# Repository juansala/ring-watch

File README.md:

# ring-watch

A watch that fits on your finger. Features an ATtiny85 and the PCF8523 real-time clock IC to change the color of an RGB LED based on the time of day.

Libraries:

TinyBMP280
SoftwareSerial
TinyWireM
RTCLib

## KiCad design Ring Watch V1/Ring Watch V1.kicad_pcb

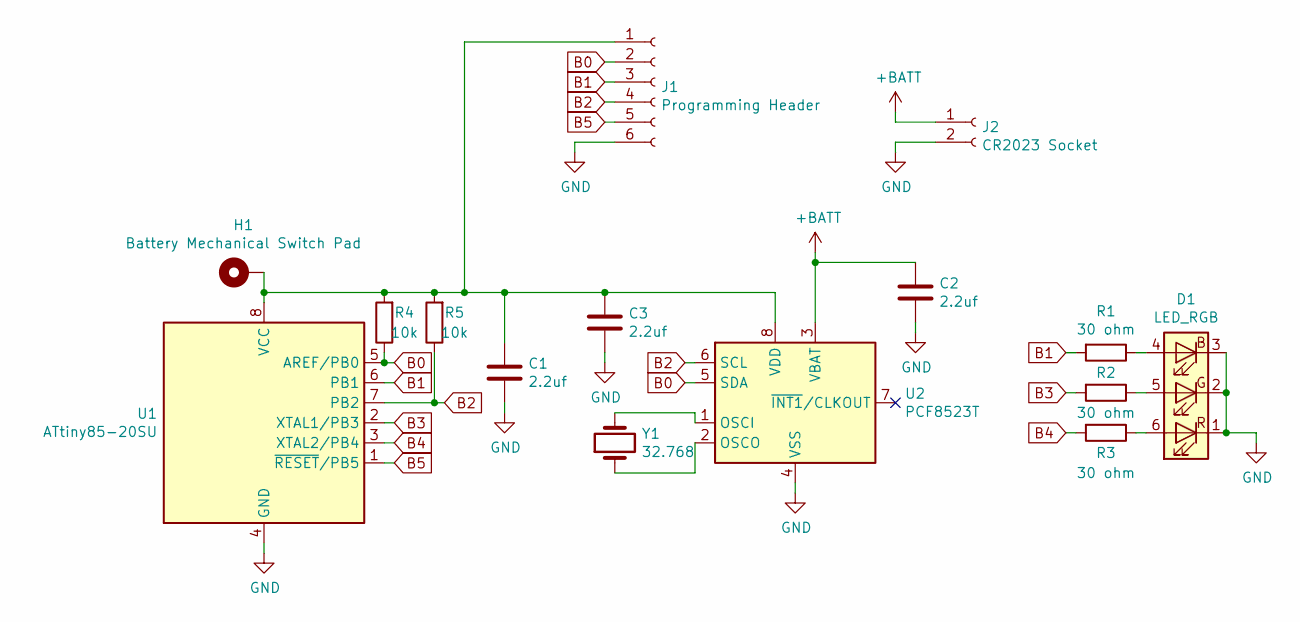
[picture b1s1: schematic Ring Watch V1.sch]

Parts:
C1, C2, C3: 2.2uf; C_0805_2012Metric_Pad1.15x1.40mm_HandSolder
D1: LED_RGB; LED_RGB_5050-6
H1: Battery Mechanical Switch Pad; TestPoint_Keystone_5019_Minature
J1: Programming Header; PinHeader_2x03_P1.00mm_Vertical
J2: CR2023 Socket; BatteryHolder_Keystone_3034_1x20mm
R1, R2, R3: 30 ohm; R_0805_2012Metric_Pad1.15x1.40mm_HandSolder
R4, R5: 10k; R_0805_2012Metric_Pad1.15x1.40mm_HandSolder
U1: ATtiny85-20SU; SOIJ-8_5.3x5.3mm_P1.27mm
U2: PCF8523T; SOIC-8_3.9x4.9mm_P1.27mm
Y1: 32.768; Crystal_SMD_3215-2Pin_3.2x1.5mm

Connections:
+BATT: C2.1, J2.1, U2.3 (VBAT)
B0: J1.2, R4.1, U1.5 (AREF/PB0), U2.5 (SDA)
B1: J1.3, R1.2, U1.6 (PB1)
B2: J1.4, R5.1, U1.7 (PB2), U2.6 (SCL)
B3: R2.2, U1.2 (XTAL1/PB3)
B4: R3.2, U1.3 (XTAL2/PB4)
B5: J1.5, U1.1 (~RESET~/PB5)
GND: C1.2, C2.2, C3.2, D1.1 (RK), D1.2 (GK), D1.3 (BK), J1.6, J2.2, U1.4 (GND), U2.4 (VSS)
unnamed: C1.1, C3.1, H1.1, J1.1, R4.2, R5.2, U1.8 (VCC), U2.8 (VDD)
unnamed: D1.4 (BA), R1.1
unnamed: D1.5 (GA), R2.1
unnamed: D1.6 (RA), R3.1
unnamed: U2.1 (OSCI), Y1.2
unnamed: U2.2 (OSCO), Y1.1

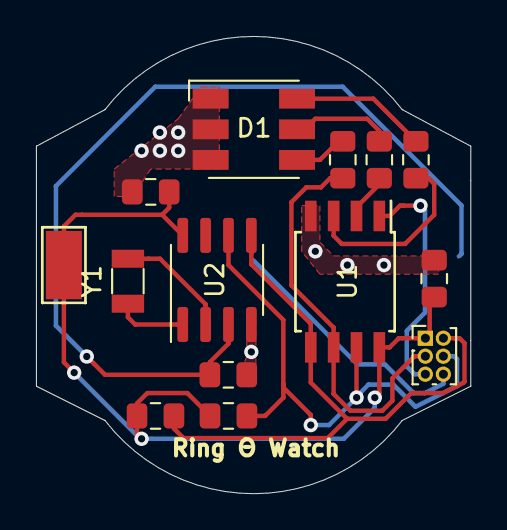
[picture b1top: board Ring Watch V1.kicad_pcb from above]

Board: 2 copper layers, 24.1 x 25.4 mm, 15 parts (1 on the bottom side), 14 nets.

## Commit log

2020-11-22 added KiCad project folder
2020-11-22 changed to ATtiny85, maybe use RGB first
2020-11-23 new mechanical switch design for input power to micro
2020-11-23 almost done placing components
2020-11-23 modified component placement
2020-11-24 more routing, board shape near final
2020-11-26 more layout changes uuggh
2020-11-27 more layout changes
2020-11-27 correct commit
2020-11-27 minor changes, need to place GND polygons
2020-11-27 added vdd cap, ground pours
2020-11-27 added name and title in silkscreen
2020-12-31 added i2c pullups
2021-01-01 changed crystal footprint, added preliminary BOMs
2021-01-01 rgb calcs, updated Digikey BOM
2021-01-21 added draft example script, rtc gives pc time
2021-01-27 added rgb led test code
2021-02-04 modified led_test script
2021-02-07 added LED control to ring_watch.ino, started FSM
2021-02-07 basic clock fsm working, added ring stl
2021-02-11 added time updates
2021-02-11 added color map
2021-02-12 commented out serial stuff b/c of pwm issues, tweaked rgb vals
2021-02-14 added minutes function
